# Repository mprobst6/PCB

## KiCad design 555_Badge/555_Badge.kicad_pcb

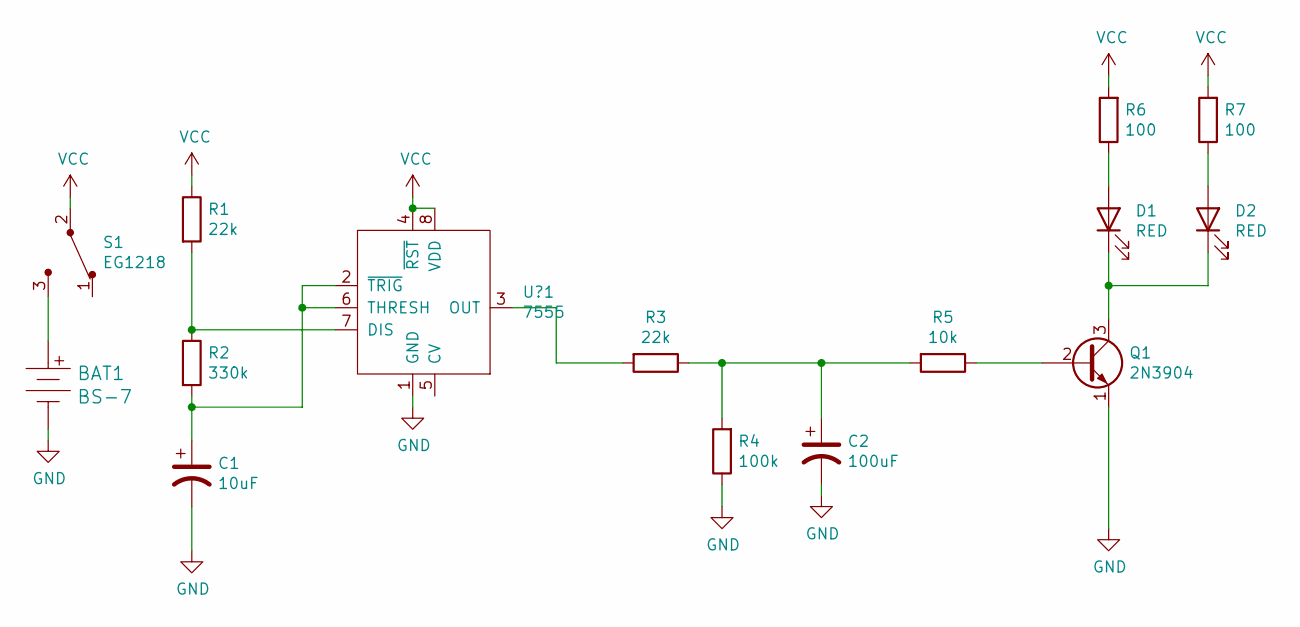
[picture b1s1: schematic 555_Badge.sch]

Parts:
BAT1: BS-7; Battery_Holder_Coin_2032_BS-7; MPN BS-7; Digi-Key_PN BS-7-ND
C1: 10uF; CP_Radial_D5.0mm_P2.00mm
C2: 100uF; CP_Radial_D6.3mm_P2.50mm
D1, D2: RED; LED_D3.0mm
Q1: 2N3904; TO-92-3
R1, R3: 22k; R_Axial_DIN0207_L6.3mm_D2.5mm_P7.62mm_Horizontal
R2: 330k; R_Axial_DIN0207_L6.3mm_D2.5mm_P7.62mm_Horizontal
R4: 100k; R_Axial_DIN0207_L6.3mm_D2.5mm_P7.62mm_Horizontal
R5: 10k; R_Axial_DIN0207_L6.3mm_D2.5mm_P7.62mm_Horizontal
R6, R7: 100; R_Axial_DIN0207_L6.3mm_D2.5mm_P7.62mm_Horizontal
S1: EG1218; Switch_Slide_11.6x4mm_EG1218; MPN EG1218; Digi-Key_PN EG1903-ND
U?1: 7555; ICM7555-PDIP

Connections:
GND: BAT1.Neg, C1.2, C2.2, Q1.1 (E), R4.1, U?1.1 (GND)
unnamed: BAT1.Pos, S1.3
unnamed: C1.1, R2.2, U?1.2 (~TRIG), U?1.6 (THRESH)
unnamed: C2.1, R3.1, R4.2, R5.2
unnamed: D1.1 (K), D2.1 (K), Q1.3 (C)
unnamed: D1.2 (A), R6.1
unnamed: D2.2 (A), R7.1
unnamed: Q1.2 (B), R5.1
unnamed: R1.2, R2.1, U?1.7 (DIS)
unnamed: R3.2, U?1.3 (OUT)
VCC: R1.1, R6.2, R7.2, S1.2, U?1.4 (~RST), U?1.8 (VDD)

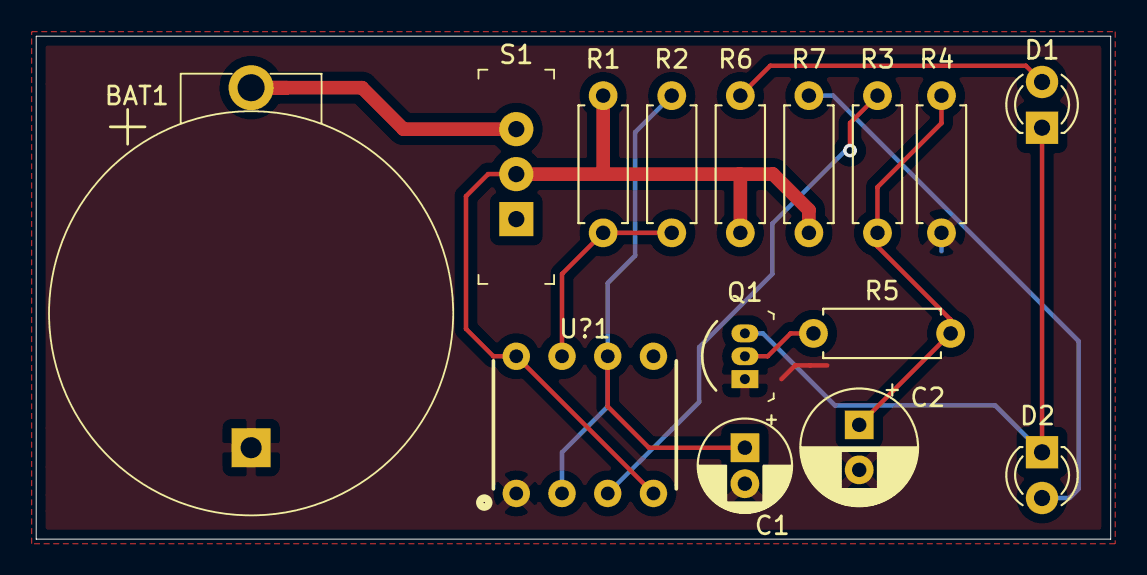
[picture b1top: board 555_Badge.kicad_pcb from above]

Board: 2 copper layers, 59.7 x 27.9 mm, 15 parts (0 on the bottom side), 11 nets.

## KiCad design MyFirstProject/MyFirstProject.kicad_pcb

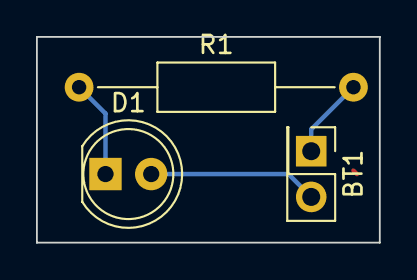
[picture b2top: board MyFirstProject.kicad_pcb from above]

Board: 2 copper layers, 19.0 x 11.4 mm, 3 parts (0 on the bottom side), 3 nets.

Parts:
BT1: 9V; PinHeader_2x01_P2.54mm_Vertical
D1: LED; LED_D5.0mm
R1: 470; R_Axial_DIN0207_L6.3mm_D2.5mm_P15.24mm_Horizontal

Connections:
unnamed: BT1.1, R1.2
unnamed: BT1.2, D1.2
unnamed: D1.1, R1.1

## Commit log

2021-12-22 Added libraries folder and finished 555 schematic
2021-12-22 Made 7555 Footprint
2021-12-22 Assigned footprints to symbols
2021-12-23 Finished board layout
2021-12-23 Added text to board layout
2021-12-23 Created Gerber Files
2021-12-23 changed name
